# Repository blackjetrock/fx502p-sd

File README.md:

# Adapter for FX-502p Calculator Interface

Adapter that allows calculator to access and SD card and GPIOs on an STM32. Allows I2c and thermal printer printouts.

 The sketch accepts commands from the 502p and stores the data
 words on the SD card under a filename specified on the 502p. This
 is a three digit number. When loading back the data words are sent
 as they were received.

 The files are FILEtnnn.DAT

    where nnn is the 3 digit file number
    and t is the type of the file:
         M for memories
         P for programs

 We leave the data line as an open drain
 output, even when we want to use it as an input. This saves the
 cycles needed to call pinMode(). Time is short when processing
 the commands from the 502p so all of the processing is done in
 interrupt routines using nested switch FSMs

 The header has been cut down to the minimum that works (50 words)
 and there's no delay when sending data words to or from the 502p.
 This means loading and saving is faster than using the FA-1

 There is code in this sketch to set and read the time and date. This
 uses a DS3231 RTC attached to the PC7 and PC6 GPIO lines on the gpio
 connector J7. On the module I used, GND and VCC lined up with GND and 3V3 on J7 
 so the code uses the GPIO lines that line up with SDA and SCL and create 
 an I2C bus on those pins.

Commands
========

The FX502P communicates with the gadget using the INV SAVE INV EXE keystroke. This saves the 
current display value to the tape interface. The commands are coded in numbers, so to issue a command 
enter the number on the calculator and then press INV SAVE INV EXE
So, for example, to display the help text page onm the OLED display you need to enter 1.0E40 and then
INV SAVE INV EXE. The help text should then be shown on the OLED display.

1.0 E40

This command displays help text on the OLED screen. Press the decimal point key to move
to the next page of help text.

1.1 E40

Display status page

1.2 E40
Display the graphics page.
Pixels can be set on this page using the graphics commands

1.3 E40
Display memory page.
This page shows memories that have been sent using an INV SAVE EXE in MODE 1

1.4 E40
Display text page. text can be placed on this page with the text commands.

1.5 E40
Display token page
This page display program tokens sent using INV SAVE EXE in MODE 3
Page using the decimal point key.

1.6 E40
This page displays the current date and time. An RTC module must be attached using I2C.

1.70 E40
Turns printing off

1.71 E40
Turns printing on

A.BC E47

This sets the current filename for programs to PABC.DAT. This is needed as even though the file number
is entered on the calculator when savng and loading that number does not go over the interface when loading.

A.BC E48

This set sthe current filename to MABC for memory saving and loading.

A.BCD E49

This sets the filename bank to ABCD. The filename banks are a way to have more than 1000 programs or memories stored on an SD card. 

Real Time Clock Commands
------------------------
This requires a DS3231 I2C real time clock module to hold the time and date. It needs to be attached to the I2C

1.0 E42 : Read date

After this is received, the date can be read using an
 
	 inv LOAD inv EXE
	  or
	 inv LOAD EXE

The date is in either the X register or the F memory
respectively.
	 
2.0 E42 : Read time

After this is received, the time can be read using an
 
	 inv LOAD inv EXE
	  or
	 inv LOAD EXE
	
respectively.

2.yymmdd E42 : Set date

3.hhmmss E42 : Set time

Text Display Commands
---------------------

Put text on the display

1.xxyy E41     
  
  Set cursor to (x,y)
  
2.aabbccdd E41   
  
3.aabbccdd E41   
  
  Print text on printer, aa etc are ascii codes

Graphics Display Commands
-------------------------

Sample Programs
---------------

The directory 

Sample_FX502P_Programs

holds some example programs.

- P998  Draws random dots on the OLED display
- 

- P999  Draws a sine wave on the OLED display

Printer
-------

The gadget can drive a simple thermal printer of the type used for receipt printing. An external PSU is required for printing due to the current requirements of the printer. Check the printer details for the curren tit uses, if it doesn't say, assume a 2A or higher PSU is needed, these printers take a lot of current. 
The attachment is on J3. there's an (unmarked) GND connection which should be attached to the PSU for the printer. The TX line sends data to the printer when enabled in the gadget.
When conneted and enabled, saving a program or memories results in the data being printed out, in ASCII.

This is the printer attached to the gadget. The black lead is GND:

This is the rear of the printer showing the connections:

The details of the printer PSU I used. This was just one I had lying about, I made a socket connection for it.

This is th eprinter I used, with some sample output.

This is the output when printing programs (ignore the memory line at the top, that is what is printed if INV SAVE INV EXE is used in MODE1):

And this is the printout of memories:

#
# Note:
# Although the FX-602P uses a similar command set it doesn't yet work with this adapter. It should be possible to make it work though.
# The FX-702p uses the same command set but operates at 5V so it also doesn't work with this adapter without some form of level shifter.

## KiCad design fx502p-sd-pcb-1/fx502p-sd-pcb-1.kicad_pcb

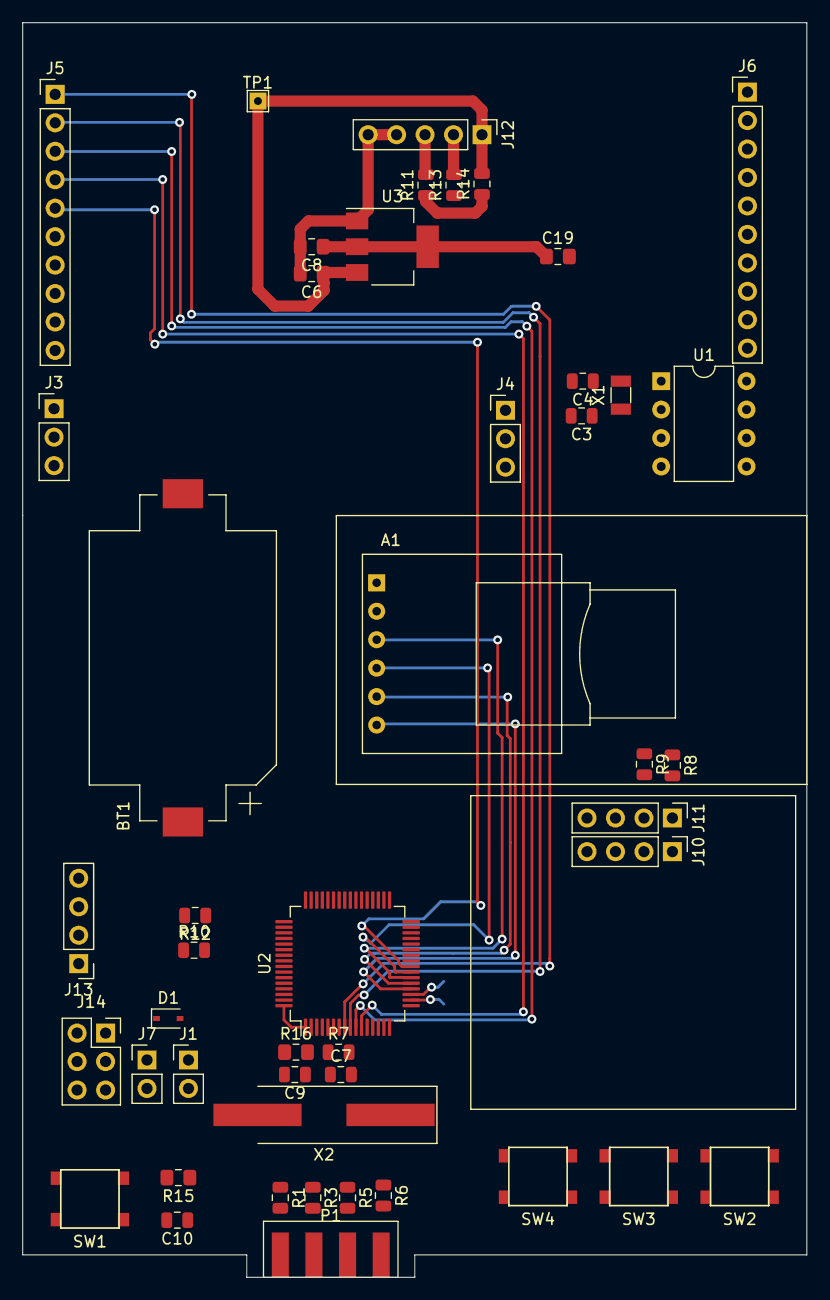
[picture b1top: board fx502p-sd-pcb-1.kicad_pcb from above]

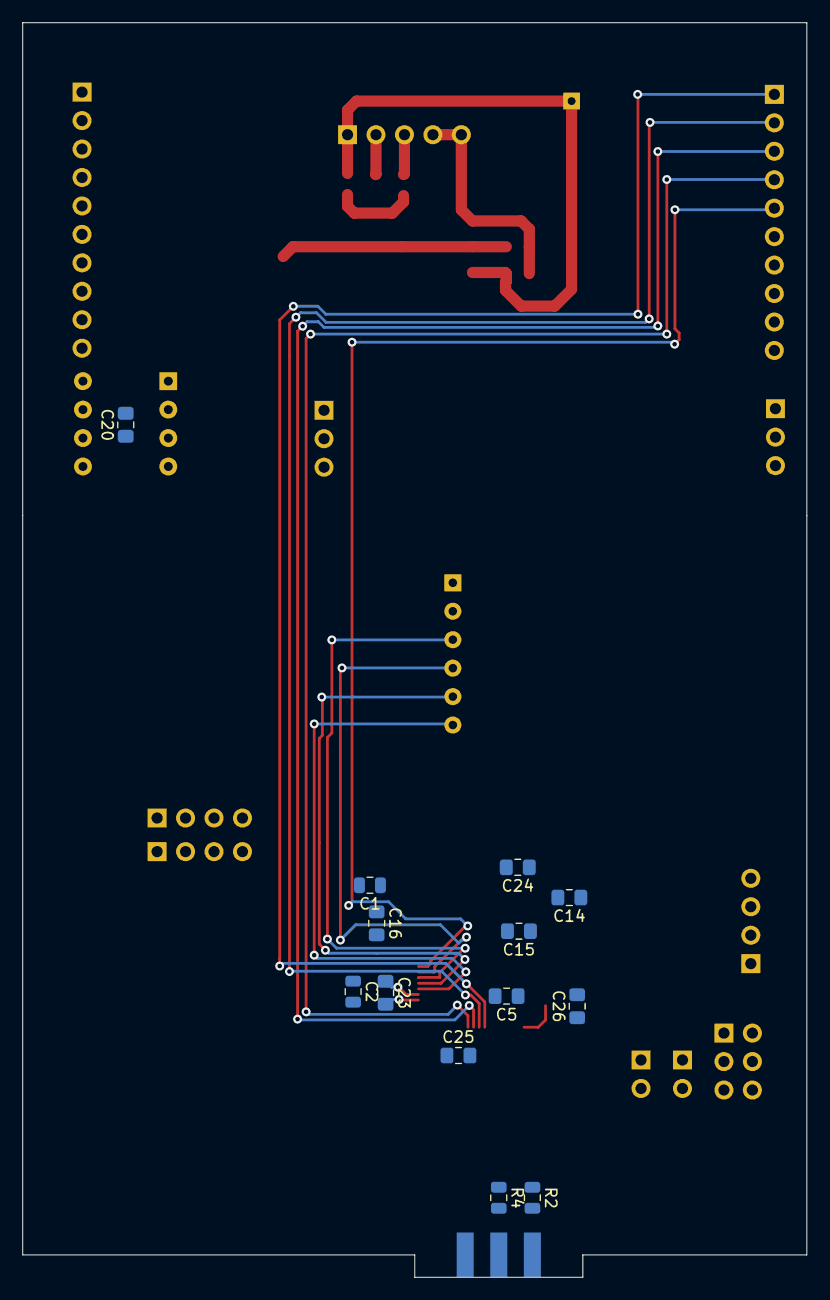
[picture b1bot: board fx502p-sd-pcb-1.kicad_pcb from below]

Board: 2 copper layers, 70.0 x 112.0 mm, 60 parts (13 on the bottom side), 62 nets.

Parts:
A1: SD_Card_Module_catalex; SD_Card_Module
BT1: Battery_Cell; BatteryHolder_Keystone_1060_1x2032
C1, C2: 100nF; C_0805_2012Metric
C3, C4, C7, C9: 10pF; C_0805_2012Metric
C5, C14, C15, C16, C19, C20, C23, C24, C25, C26: 100nF; C_0805_2012Metric_Pad1.15x1.40mm_HandSolder
C6, C8: 1uF; C_0805_2012Metric_Pad1.15x1.40mm_HandSolder
C10: 1uF; C_0805_2012Metric
D1: D; D_SOD-323
J1, J7: Conn_01x02_Male; PinHeader_1x02_P2.54mm_Vertical
J3: Conn_01x03_Female; PinHeader_1x03_P2.54mm_Vertical
J4: Conn_01x03_Male; PinHeader_1x03_P2.54mm_Vertical
J5, J6: Conn_01x10_Male; PinHeader_1x10_P2.54mm_Vertical
J10, J11: Conn_01x04_Male; PinHeader_1x04_P2.54mm_Vertical
J12: Conn_01x05; PinHeader_1x05_P2.54mm_Vertical
J13: Conn_01x04; PinHeader_1x04_P2.54mm_Vertical
J14: Conn_02x03_Odd_Even; PinSocket_2x03_P2.54mm_Vertical
P1: Expansion; expansion_fx502p
R1, R2, R3, R4, R5, R6, R8, R9: R_Small; R_0805_2012Metric
R7: 390R; R_0805_2012Metric
R10, R12: 10k; R_0805_2012Metric
R11, R13: 20R; R_0805_2012Metric
R14: 4k7; R_0805_2012Metric
R15: 10k; R_0805_2012Metric_Pad1.15x1.40mm_HandSolder
R16: 1M; R_0805_2012Metric_Pad1.15x1.40mm_HandSolder
SW1, SW2, SW3, SW4: Switch_SW_SPST; SMD_BUTTON
TP1: TestPoint; TestPoint_THTPad_1.5x1.5mm_Drill0.7mm
U1: MCP7940N-xSN; DIP-8_W7.62mm
U2: STM32F103RGTx; LQFP-64_10x10mm_P0.5mm
U3: AMS1117-3.3; SOT-223-3_TabPin2
X1: 32.768kHz; Crystal_SMD_3215-2Pin_3.2x1.5mm
X2: 8MHz; Crystal_SMD_HC49-SD_HandSoldering

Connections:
+3V3: C2.1, C5.1, C8.1, C14.1, C15.1, C16.1, C19.1, C20.1, C23.1, C24.1, C25.1, C26.1, J1.1, J4.1, J5.9, J6.9, J10.3, J11.4, J13.1, J14.1, J14.2, R8.1, R9.1, R15.1, U1.8, U2.1, U2.13, U2.19, U2.32, U2.48, U2.64, U3.2
+5V: A1.2, C6.1, J12.1, R14.2, TP1.1, U3.3
BOOT0: R10.2, U2.60
BOOT1: R12.1, U2.28
CALC_CE: R1.1, U2.34
CALC_CONT: R4.1, U2.36
CALC_D3: R3.1, U2.55
CALC_GND: A1.1, BT1.2, C1.2, C2.2, C3.2, C4.2, C5.2, C6.2, C7.2, C8.2, C9.2, C10.2, C14.2, C15.2, C16.2, C19.2, C20.2, C23.2, C24.2, C25.2, C26.2, J3.1, J5.10, J6.10, J10.4, J11.3, J12.4, J12.5, J13.4, J14.5, J14.6, P1.6, SW1.2, SW2.2, SW3.2, SW4.2, U1.4, U2.12, U2.18, U2.31, U2.47, U2.63, U3.1
CALC_OP: R5.1, U2.56
CALC_SP: R6.1, U2.33
CALC_VCC: D1.1, J7.1, U2.35
NRST: C10.1, R15.2, SW1.1, U2.7
unnamed: BT1.1, J4.3
unnamed: C1.1, J4.2, U1.3
unnamed: C3.1, U1.2, X1.2
unnamed: C4.1, U1.1, X1.1
unnamed: D1.2, J1.2
unnamed: J5.1, U2.8
unnamed: J5.2, U2.9
unnamed: J5.3, U2.10
unnamed: J5.4, U2.11
unnamed: J5.5, U2.24
unnamed: J5.6, U2.25
unnamed: J5.7, U2.37
unnamed: J5.8, U2.38
unnamed: J6.1, U2.39
unnamed: J6.2, U2.40
unnamed: J6.3, U2.51
unnamed: J6.4, U2.52
unnamed: J6.5, U2.53
unnamed: J6.6, U2.2
unnamed: J6.7, U2.3
unnamed: J6.8, U2.4
unnamed: J7.2, R2.1
unnamed: J12.2, R13.2
unnamed: J12.3, R11.2
unnamed: J14.3, R10.1
unnamed: J14.4, R12.2
unnamed: P1.1, R1.2
unnamed: P1.2, R2.2
unnamed: P1.3, R3.2
unnamed: P1.4, R4.2
unnamed: P1.5, R5.2
unnamed: P1.7, R6.2
unnamed: R7.2, U2.6
unnamed: SW2.1, U2.14
unnamed: SW3.1, U2.15
unnamed: SW4.1, U2.16
OSCI: C7.1, R16.2, U2.5, X2.1
OSCO: C9.1, R7.1, R16.1, X2.2
PA11: R13.1, U2.44
PA12: R11.1, R14.1, U2.45
RX: J3.2, U2.43
SCL: J10.2, J11.2, R9.2, U1.6, U2.29
SDA: J10.1, J11.1, R8.2, U1.5, U2.30
SD_CLK: A1.5, U2.21
SD_CS: A1.6, U2.20
SD_MISO: A1.3, U2.22
SD_MOSI: A1.4, U2.23
SWDCLK: J13.3, U2.49
SWDIO: J13.2, U2.46
TX: J3.3, U2.42

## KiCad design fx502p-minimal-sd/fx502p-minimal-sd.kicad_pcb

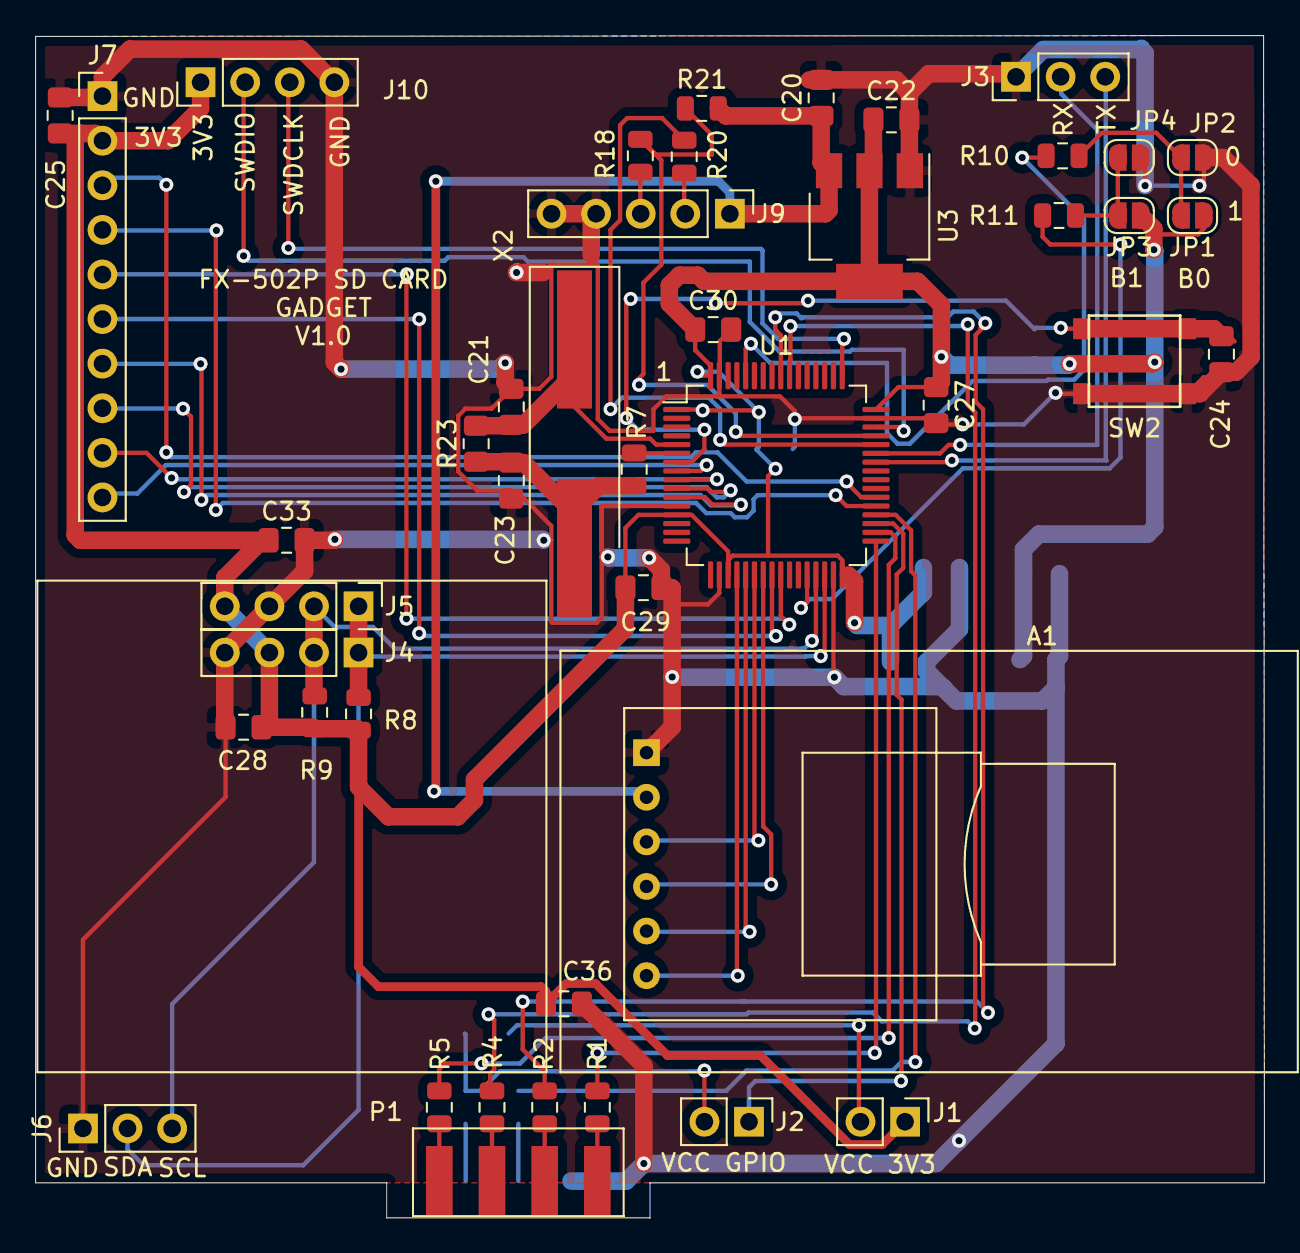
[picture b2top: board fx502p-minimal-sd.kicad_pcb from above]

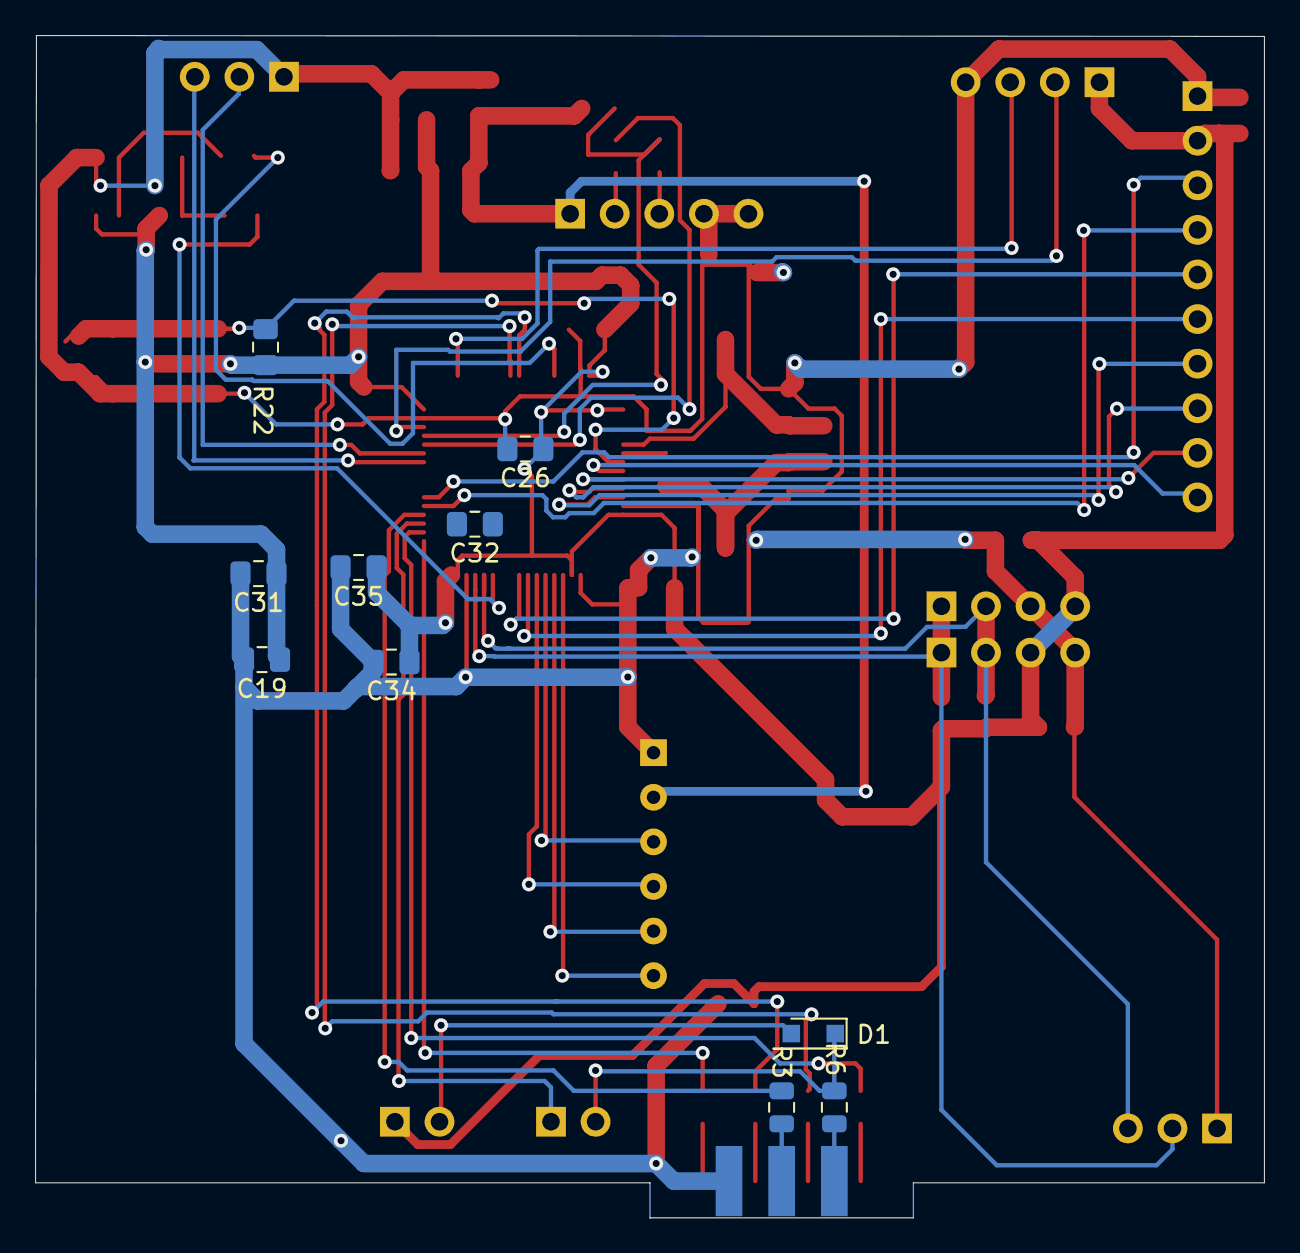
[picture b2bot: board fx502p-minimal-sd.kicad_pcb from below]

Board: 2 copper layers, 70.0 x 67.3 mm, 54 parts (10 on the bottom side), 47 nets.

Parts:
A1: SD_Card_Module_catalex; SD_Card_Module
C19, C25, C26, C27, C28, C29, C30, C31, C32, C33, C34, C35, C36: 100nF; C_0805_2012Metric_Pad1.15x1.40mm_HandSolder
C20, C22, C24: 1uF; C_0805_2012Metric_Pad1.15x1.40mm_HandSolder
C21, C23: 10pF; C_0805_2012Metric_Pad1.15x1.40mm_HandSolder
D1: D; D_SOD-323_HandSoldering
J1, J2: Conn_01x02_Male; PinHeader_1x02_P2.54mm_Vertical
J3, J6: Conn_01x03_Female; PinHeader_1x03_P2.54mm_Vertical
J4, J5: Conn_01x04_Male; PinHeader_1x04_P2.54mm_Vertical
J7: Conn_01x10_Female; PinHeader_1x10_P2.54mm_Vertical
J9: Conn_01x05; PinHeader_1x05_P2.54mm_Vertical
J10: Conn_01x04; PinHeader_1x04_P2.54mm_Vertical
JP1, JP2, JP3, JP4: Jumper; SolderJumper-2_P1.3mm_Open_RoundedPad1.0x1.5mm
P1: Expansion; expansion_fx502p
R1, R2, R3, R4, R5, R6: R_Small; R_0805_2012Metric
R7: 390R; R_0805_2012Metric
R8, R9, R21: 4k7; R_0805_2012Metric
R10, R11: 10k; R_0805_2012Metric
R18, R20: 20R; R_0805_2012Metric
R22: 10k; R_0805_2012Metric_Pad1.15x1.40mm_HandSolder
R23: 1M; R_0805_2012Metric_Pad1.15x1.40mm_HandSolder
SW2: Switch_SW_SPST; SMD_BUTTON
U1: STM32F103RGTx; LQFP-64_10x10mm_P0.5mm
U3: AMS1117-3.3; SOT-223-3_TabPin2
X2: 8MHz; Crystal_SMD_HC49-SD_HandSoldering

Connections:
+3V3: C19.1, C22.1, C25.1, C26.1, C27.1, C28.1, C29.1, C30.1, C31.1, C33.1, C34.1, C35.1, C36.1, J1.1, J4.3, J5.4, J7.2, J10.1, JP1.1, JP3.1, R8.1, R9.1, R22.1, U1.1, U1.13, U1.19, U1.32, U1.48, U1.64, U3.2
+5V: A1.2, C20.1, J9.1, R21.2, U3.3
BOOT0: R10.1, U1.60
BOOT1: R11.1, U1.28
CALC_CE: R5.1, U1.34
CALC_CONT: R3.1, U1.36
CALC_D3: R4.1, U1.55
CALC_GND: A1.1, C19.2, C20.2, C21.2, C22.2, C23.2, C24.2, C25.2, C26.2, C27.2, C28.2, C29.2, C30.2, C31.2, C33.2, C34.2, C35.2, C36.2, J3.1, J4.4, J5.3, J6.1, J7.1, J9.4, J9.5, J10.4, JP2.1, JP4.1, P1.6, SW2.2, U1.12, U1.18, U1.31, U1.47, U1.63, U3.1
CALC_OP: R2.1, U1.56
CALC_SP: R1.1, U1.33
CALC_VCC_GPIO: J2.1, U1.35
NRST: C24.1, R22.2, SW2.1, U1.7
unnamed: D1.1, J2.2, R6.1
unnamed: D1.2, J1.2
unnamed: J7.3, U1.38
unnamed: J7.4, U1.37
unnamed: J7.5, U1.25
unnamed: J7.6, U1.24
unnamed: J7.7, U1.11
unnamed: J7.8, U1.10
unnamed: J7.9, U1.9
unnamed: J7.10, U1.8
unnamed: J9.2, R20.2
unnamed: J9.3, R18.2
unnamed: JP1.2, JP2.2, R10.2
unnamed: JP3.2, JP4.2, R11.2
unnamed: P1.1, R5.2
unnamed: P1.2, R6.2
unnamed: P1.3, R4.2
unnamed: P1.4, R3.2
unnamed: P1.5, R2.2
unnamed: P1.7, R1.2
unnamed: R7.2, U1.6
OSCI: C21.1, R23.2, U1.5, X2.1
OSCO: C23.1, R7.1, R23.1, X2.2
PA11: R20.1, U1.44
PA12: R18.1, R21.1, U1.45
RX: J3.2, U1.43
SCL: J4.2, J5.2, J6.3, R9.2, U1.29
SDA: J4.1, J5.1, J6.2, R8.2, U1.30
SD_CLK: A1.5, U1.21
SD_CS: A1.6, U1.20
SD_MISO: A1.3, U1.22
SD_MOSI: A1.4, U1.23
SWDCLK: J10.3, U1.49
SWDIO: J10.2, U1.46
TX: J3.3, U1.42

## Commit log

2020-12-28 Initial check in
2020-12-30 Added traces and made sketch changes
2021-01-01 Added traces and sketch now works with internal tracing in buffer
2021-01-01 Sketch updates to the point that the start of an inv save inv exe can be received.
2021-01-02 Latest sketch, not working too well.
2021-01-02 Sketch has has pinmode removed. Seems to capture inv save inv exe data. Got display register information from a trace manually.
2021-01-02 Sketch has packet count removed. Manages to count now due to packet_count vs word_length bug.
2021-01-02 Sketch has received mode 1 and mode 3 data. Data in mode 3 decoded to a valid represenation of the program loaded in P0
2021-01-02 Captured words decoded to programs
2021-01-05 Sketch can now pretty reliably receive a file from a 502p. The serial monitor has to be disabled, it appears, as it seems to disable interrupts. That causes errors on the data stream interrupt proces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
2021-01-05 Created a Tcl script to decode the FX-502P files.
2021-01-05 Updated file utility
2021-01-06 Sketch now receives and writes files to SD. Sending back is in there, but doesn't work for some reason.
2021-01-07 Added some files that were written by the gadget after a SAVE on a 502p. Updates to the file decoder and the sketch. Storing data with the SAVE command to SD card works with this version. LOADing bac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
2021-01-07 Fixed edit problem
2021-01-07 Updated decode of files.
2021-01-08 Sketch now loads as well as saves. Added data file from an FA-1 load using laptop.
2021-01-09 Updates to sketch, and misc other files
2021-01-09 Added git ignore file.
2021-01-09 Tidy up
2021-01-09 The 1x 10^48 special exponent now works. Both M and P files can be loaded using inv SAVE inv EXE
    x.yz * 10^47 for Pxyz
    x.yz * 10^48 for Mxyz
2021-01-09 Data line now comes up in benign state. Leaving it as LOW strangely caused M1 to change from 1111 to 11.11
2021-01-09 Script update
2021-01-09 Added stored files.
2021-01-12 Created a minimal PCB as a first attempt at PCB sizes etc. If this works then maybe do the full card with lots of IO that I was starting with.
2021-01-21 Added notes file
2021-01-21 Modified permissions
2021-01-27 Modified to run on the larger STM32F103RE (or larger) This is a 64 pin package. The OLED display is on Wire2 so needed an adjustment. All else seems fine and it has run on a 502P
2021-01-27 Starting to add fiunctions to decode memories.
2021-01-27 Added more menu optiosn ot try to get to editing of buffer. Now doesn't work
2021-01-27 Turned monitor off during rx. Didn't make this build work again
2021-01-28 Adding memory decode and found that when code size increases the interface to the calculator stops working. It looks like CE interrupt is late relative to the clock.
2021-01-29 Fixed save, load still doesn't work. The fix was to add a hint length for the next packet. When that is reached we do an end-of-packet action. This is because the OP ISr seems to be out of sequence (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
2021-01-29 the SAVE and LOAD is now working on fx502p using any code size. The problem seems to be that when the OP GPIO line is read it doesn't read the current pin state. reading the GPIO later in the ISR see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
2021-01-29 Tidy up.
2021-01-29 Updates. Added LED toggle on PC3 when fiel written. Crude way for calc to drive GPIO port.
2021-01-29 Added modification of data words.
2021-01-29 Added mem command that decodes the memories.
2021-01-29 Memory decode now handles exponents and signs.
2021-01-30 Added memory display mode 1.1 e 40 inv save inv exe to turn on 1.0 e 40 inv save inv exe to turn off Displays 8 memories on OLED after save of memories.
2021-02-02 Added noteson undefined opcodes in programs and a case/ holder for PCB
2021-02-04 Added the softwire library so I2C should be accessible on the GPIO port. Doesn't work on DS3231 RTC for some reason.
2021-02-04 Added some files
2021-02-04 Updated git ignore file
2021-02-04 Update to sketch
2021-02-04 Added text mode display
2021-02-06 Added handlers for the . and AC keys and multiple help pages
2021-02-06 Added program display. Shows the currently loaded data words as a program in text form. Has word wrap. As it won't all fit on one page, the dot key can be used to page the display.
    Also had a nasty emacs editing problem. Everything seems to be recovered but there could be lingering problems.
2021-02-08 Added an execution engine, or the start of it.
2021-02-11 Fixed the clock routine that reads an attached I2C RTC DS3231 on test module.
2021-02-11 Added clock display and two commands to set the time and date.
2021-02-12 Added time and date commands that access an attached DS3231 on the GPIO lines.
2021-02-14 Updates for temperature/light/pot ADC/DA sensor PCF8951
2021-02-23 Added basic support for a receipt printer attached to expansion GPIO header
2021-02-23 Tidied up printing. Added 1.70e40 and 1.71e40 to turn print flag off and on. Memory print out now stops on invalid entries.
2021-02-27 Updates to prog engine. It now runs a few instructions.
2021-03-22 Works as a basic calculator
2021-03-23 Added more functions. Number entry requires a complete rewrite.
2021-06-04 Sorted leading zero problem of .xxxx numbers.
2022-08-22 Removed serial output as it stopped the software serial code from driving the printer once it had initialised (the serial library).
2022-08-23 Fixed debug code in text screen
